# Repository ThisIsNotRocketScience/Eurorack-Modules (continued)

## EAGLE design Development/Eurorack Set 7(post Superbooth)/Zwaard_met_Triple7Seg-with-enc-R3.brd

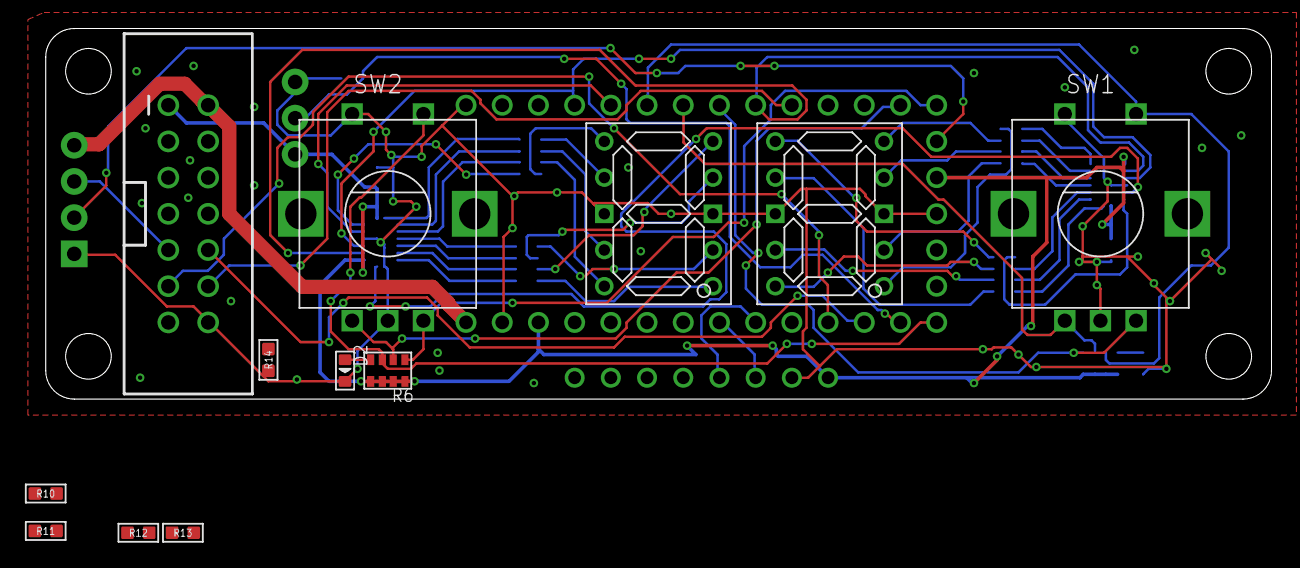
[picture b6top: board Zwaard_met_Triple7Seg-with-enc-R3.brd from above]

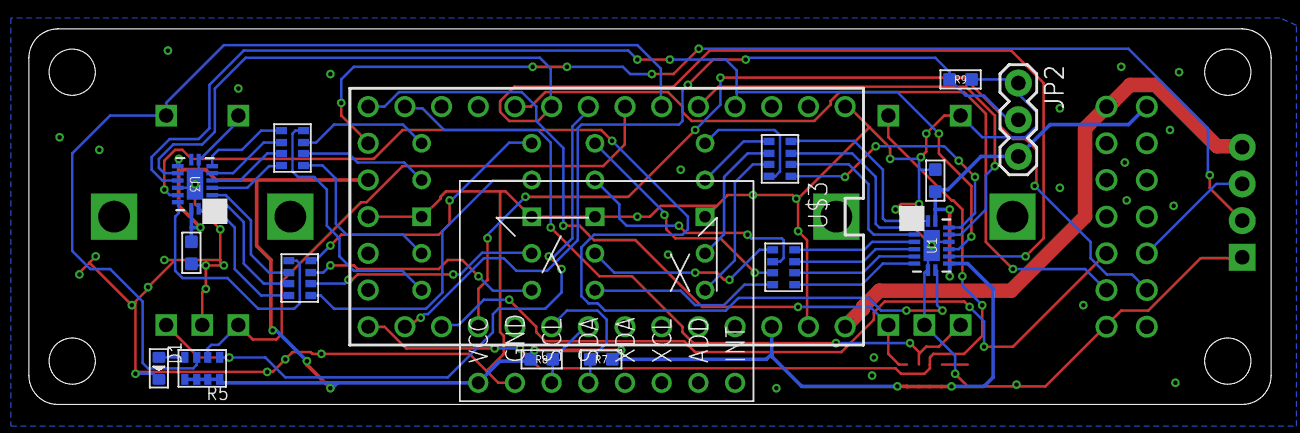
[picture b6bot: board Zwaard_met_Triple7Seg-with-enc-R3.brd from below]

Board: 2 copper layers, 86.0 x 26.0 mm, 29 parts (16 on the bottom side), 61 nets.

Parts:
C1, C2: 100n; C0603
D1, D2: LED0603
JP1: 1X04
JP2: 1X03
R1, R2, R3, R4: 56; R1206-8
R5, R6: R1206-8
R7, R8: 2k; R0603
R9, R10, R11, R12, R13, R14: 10k; R0603
SW1, SW2: EC12E_SW; ALPS_EC12E_SW
U1, U3: 74HCT595BQ; QFN50P250X350X100-17N
U$1, U$4: 7.1SEG; 7SEG_500X400MIL
U$3: TEENSY_LC_OUTER_ROW; TEENSY_3.0-3.2&LC_OUTER_ROW
U$6: ACCELERO; ACCELBOARD
U$7: M07X2; 2X70SHROUDED_LOCK

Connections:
3.3V: C1.1, C2.1, JP2.3, R5.5, R5.6, R5.7, R5.8, R6.5, R6.6, R6.7, R6.8, R7.1, R8.1, U1.10, U1.16, U3.10, U3.16, U$3.3.3V, U$3.3.3V1, U$6.VCC, U$7.1
5V: JP1.4, U$3.VIN, U$7.2
A: R1.8, U$1.1
A2: R3.8, U$4.1
B: R1.5, U$1.2
B2: R3.5, U$4.2
C: R1.6, U$1.3
C2: R3.6, U$4.3
D: R1.7, U$1.4
D2: R3.7, U$4.4
E: R2.5, U$1.6
E2: R4.5, U$4.6
ENC1_A: R5.2, SW1.A, U$3.5
ENC1_B: R5.1, SW1.B, U$3.6
ENC1_S: R5.3, SW1.E, U$3.4
ENC2_A: R6.2, SW2.A, U$3.11
ENC2_B: R6.1, SW2.B, U$3.12
ENC2_S: R6.3, SW2.E, U$3.13
F: R2.6, U$1.7
F2: R4.6, U$4.7
G: R2.7, U$1.8
G2: R4.7, U$4.8
GND: C1.2, C2.2, D1.-, D2.-, JP1.1, JP2.1, R9.1, R12.1, SW1.C, SW1.D, SW2.C, SW2.D, U1.8, U1.13, U1.17, U3.8, U3.13, U3.17, U$1.GNDA, U$1.GNDB, U$3.AGND, U$3.GND, U$3.GND1, U$4.GNDA, U$4.GNDB, U$6.GND, U$7.14
H: R2.8, U$1.5
H2: R4.8, U$4.5
LED1: R10.1, U$3.9
LED1OUT: R10.2, U$7.3
LED2: R11.1, U$3.10
LED2OUT: R11.2, U$7.4
LEDCLK: U1.11, U3.11, U$3.7
LEDDAT: U1.14, U$3.3
LEDLATCH: U1.12, U3.12, U$3.2
LED_DATA_OUT: JP1.2, U$3.VBAT
LED_NAAR_RING: JP1.3, U$7.9
unnamed: D1.+, R5.4
unnamed: D2.+, R6.4
unnamed: R1.4, U1.1
unnamed: R1.3, U1.2
unnamed: R1.2, U1.3
unnamed: R2.4, U1.4
unnamed: R2.3, U1.5
unnamed: R2.2, U1.6
unnamed: R2.1, U1.7
unnamed: R1.1, U1.15
unnamed: R3.4, U3.1
unnamed: R3.3, U3.2
unnamed: R3.2, U3.3
unnamed: R4.4, U3.4
unnamed: R4.3, U3.5
unnamed: R4.2, U3.6
unnamed: R4.1, U3.7
unnamed: R3.1, U3.15
unnamed: R12.2, R13.1
POT1: R14.2, U$7.10
POT_1_IN: R13.2, R14.1, U$3.15/A1
POT_2: U$3.16/A2, U$7.11
SCL: R8.2, U$3.19/A5, U$6.SCL
SDA: R7.2, U$3.18/A4, U$6.SDA
SEG2DAT: U1.9, U3.14
SOFTPOT: JP2.2, R9.2, U$3.14/A0
SWITCH: U$3.8, U$7.12

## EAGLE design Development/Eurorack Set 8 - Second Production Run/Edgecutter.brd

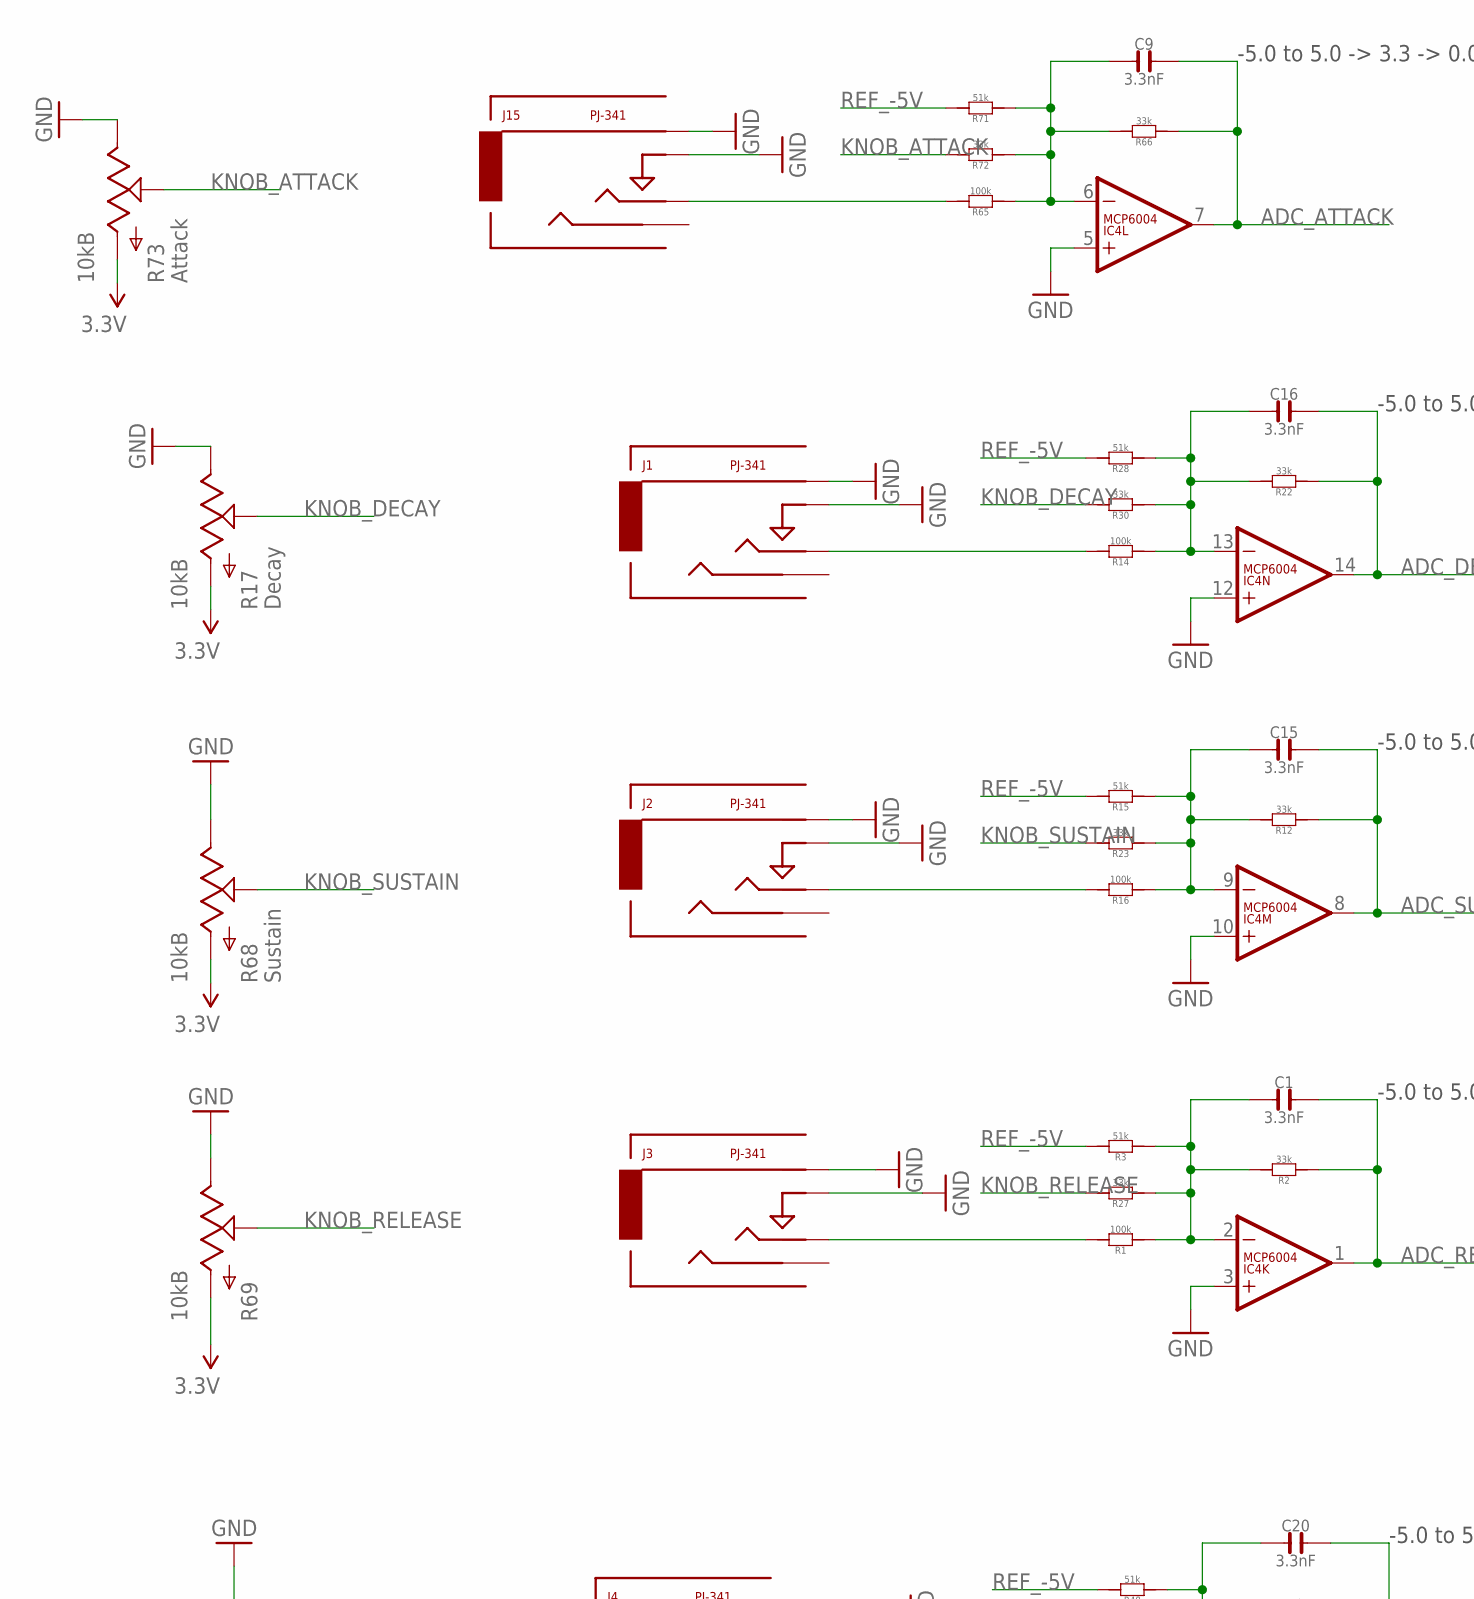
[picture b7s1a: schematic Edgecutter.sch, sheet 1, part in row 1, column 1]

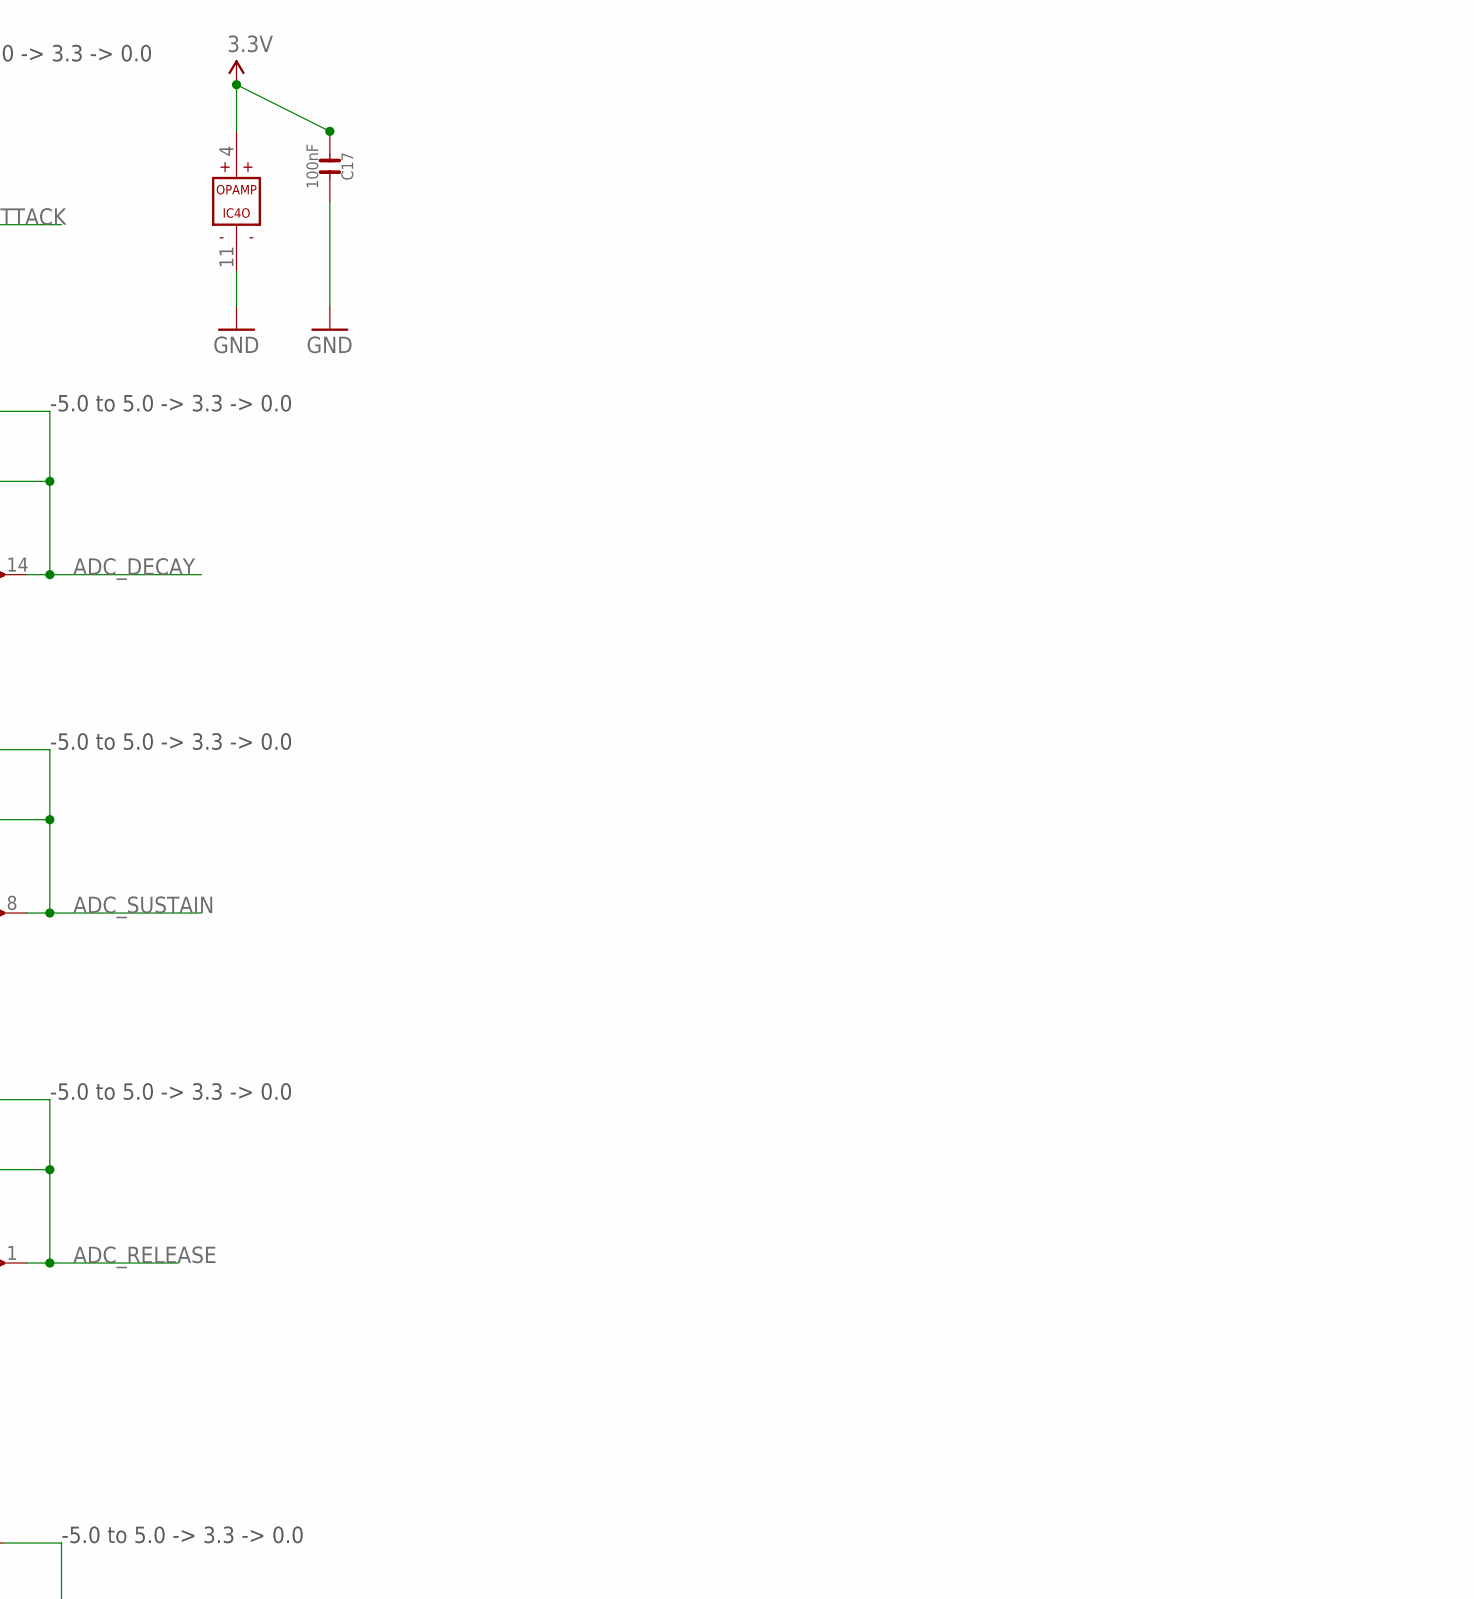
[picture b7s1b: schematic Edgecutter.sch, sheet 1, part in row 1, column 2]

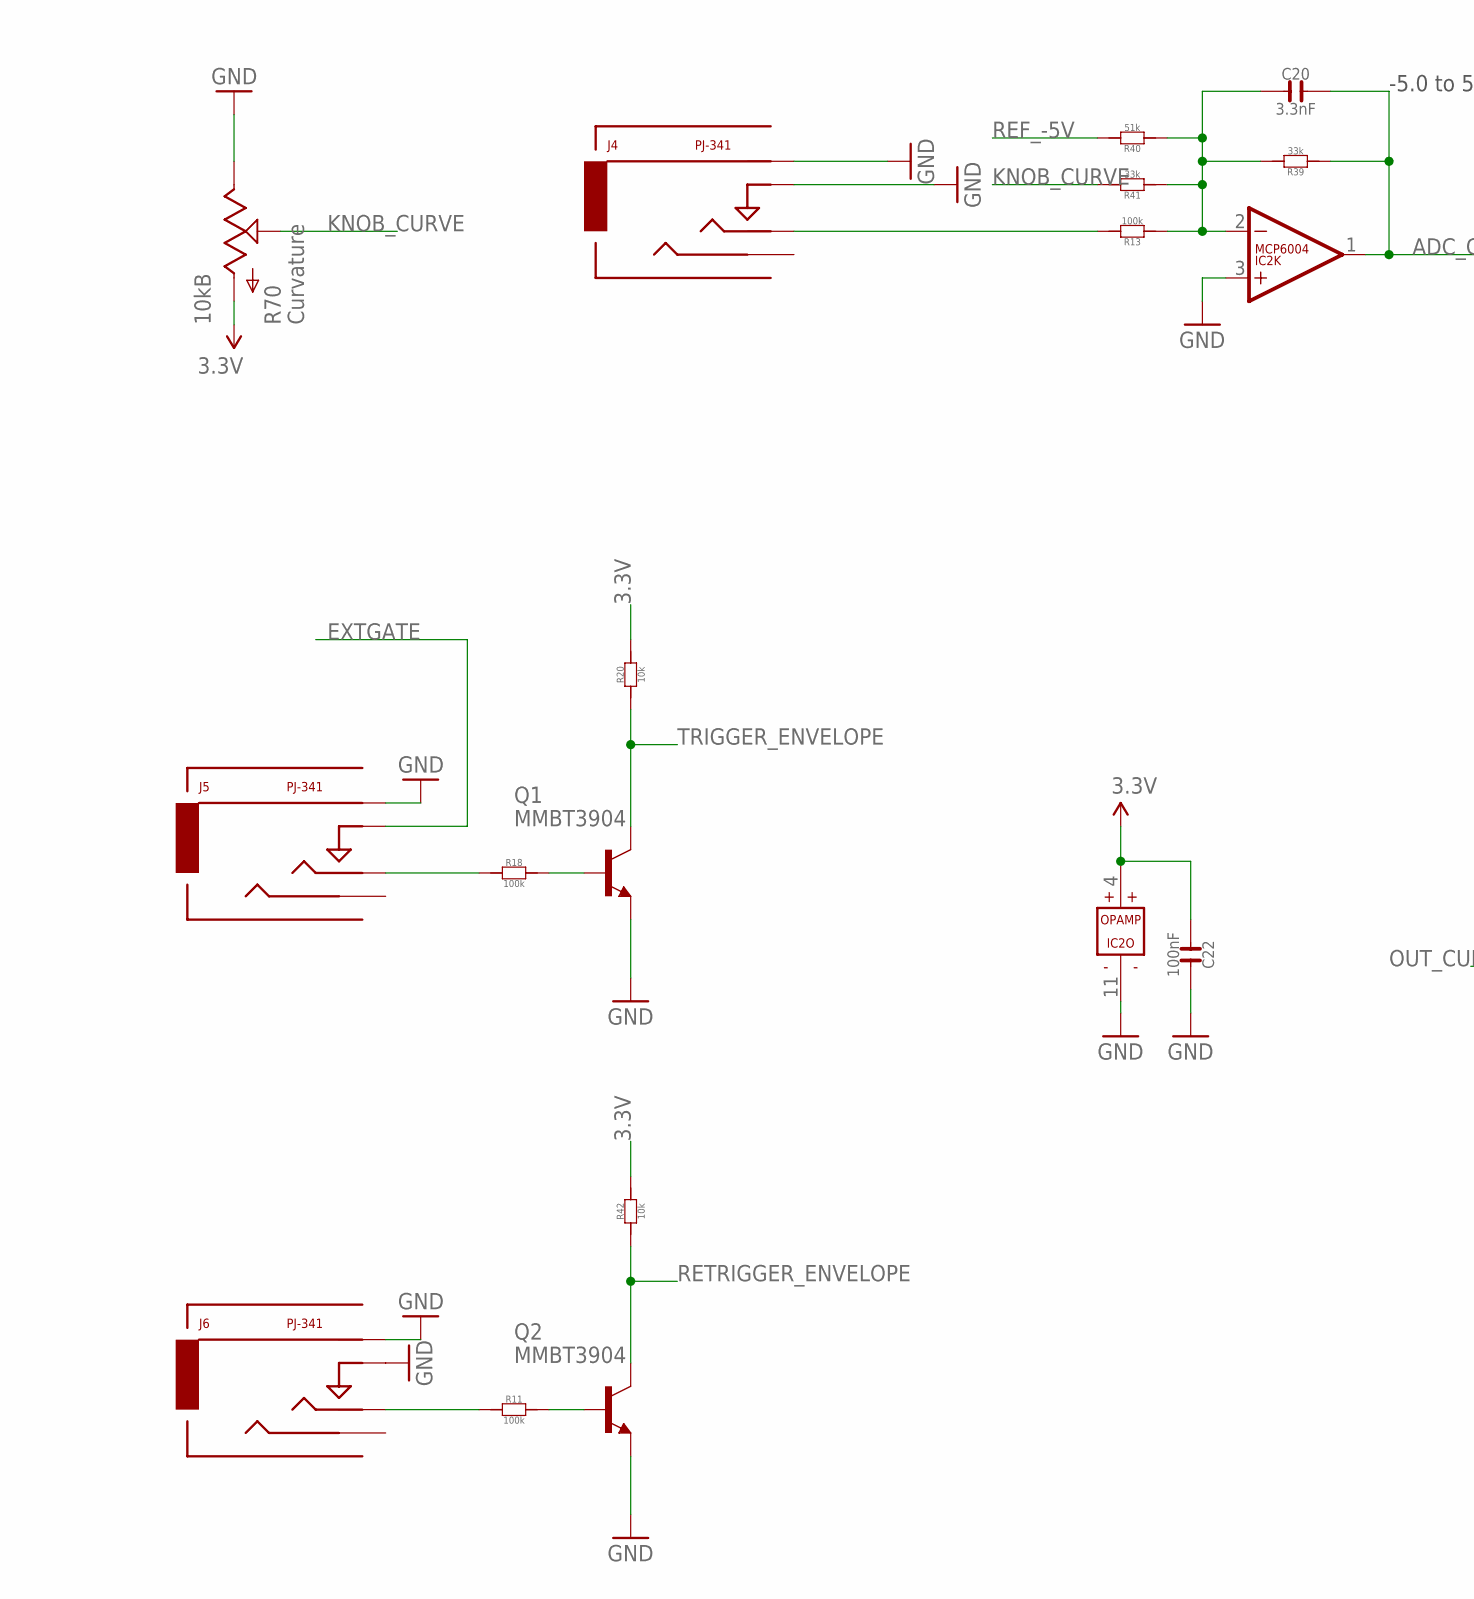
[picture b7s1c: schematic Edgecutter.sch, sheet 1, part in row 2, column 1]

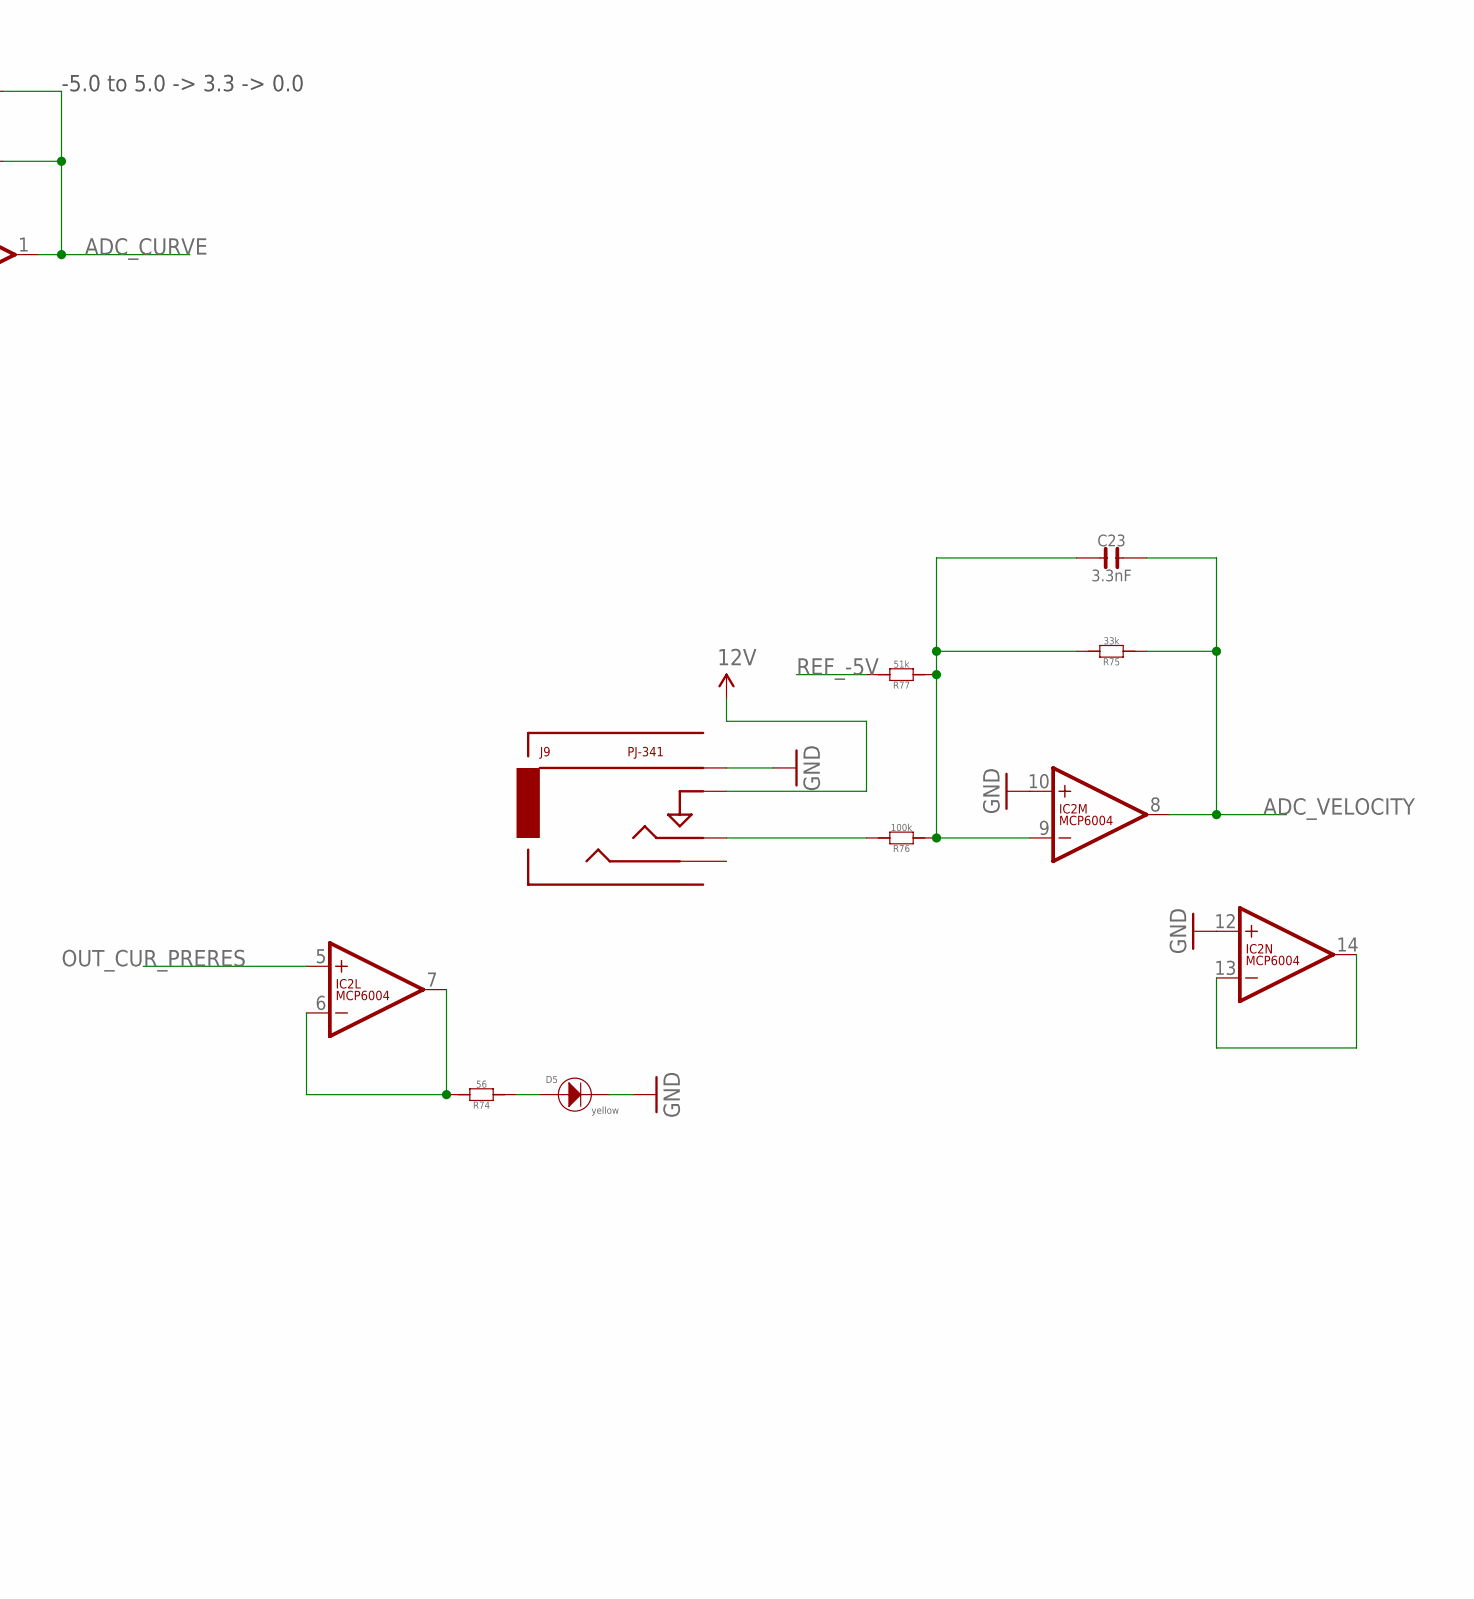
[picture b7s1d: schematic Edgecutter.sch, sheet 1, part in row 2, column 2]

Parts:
C1, C9, C15, C16, C20, C23: 3.3nF; C0603
C17, C22: 100nF; C0603; MPN MC0603F104Z160CT
D5: yellow; 3MMLED
IC2, IC4: MCP6004; SO14; MPN MCP6004-I/SL.
J1, J2, J3, J4, J5, J6, J9, J15: PJ-341; 3.5MM-JACK-SWITCH-13MM-INPUT
Q1, Q2: MMBT3904; SOT23-BEC; MPN PMBT3904,215
R1, R11, R13, R14, R16, R18, R65, R76: 100k; R0603
R2, R12, R22, R23, R27, R30, R39, R41, R66, R72, R75: 33k; R0603
R3, R15, R28, R40, R71, R77: 51k; R0603
R17, R68, R69, R70, R73: 10kB; OG-POTS_ALPS_POT_VERTICAL
R20, R42: 10k; R0603
R74: 56; R0603

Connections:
3.3V: C17.1, C22.1, IC2.4 (V+), IC4.4 (V+), R17.P$3 (A), R20.2, R42.2, R68.P$3 (A), R69.P$3 (A), R70.P$3 (A), R73.P$3 (A); also elsewhere on the board
12V: J9.SWITCH@3 (SWITCH); also elsewhere on the board
ADC_ATTACK: C9.2, IC4.7 (OUT), R66.1; also elsewhere on the board
ADC_CURVE: C20.2, IC2.1 (OUT), R39.1; also elsewhere on the board
ADC_DECAY: C16.2, IC4.14 (OUT), R22.1; also elsewhere on the board
ADC_RELEASE: C1.2, IC4.1 (OUT), R2.1; also elsewhere on the board
ADC_SUSTAIN: C15.2, IC4.8 (OUT), R12.1; also elsewhere on the board
ADC_VELOCITY: C23.2, IC2.8 (OUT), R75.1; also elsewhere on the board
EXTGATE: J5.SWITCH@3 (SWITCH); also elsewhere on the board
GND: C17.2, C22.2, D5.-, IC2.3 (+IN), IC2.10 (+IN), IC2.11 (V-), IC2.12 (+IN), IC4.3 (+IN), IC4.5 (+IN), IC4.10 (+IN), IC4.11 (V-), IC4.12 (+IN), J1.RING@3 (RING), J1.SWITCH@3 (SWITCH), J2.RING@3 (RING), J2.SWITCH@3 (SWITCH), J3.RING@3 (RING), J3.SWITCH@3 (SWITCH), J4.RING@3 (RING), J4.SWITCH@3 (SWITCH), J5.RING@3 (RING), J6.RING@3 (RING), J6.SWITCH@3 (SWITCH), J9.RING@3 (RING), J15.RING@3 (RING), J15.SWITCH@3 (SWITCH), Q1.E, Q2.E, R17.P$1 (E), R68.P$1 (E), R69.P$1 (E), R70.P$1 (E), R73.P$1 (E); also elsewhere on the board
KNOB_ATTACK: R72.2, R73.P$2 (S)
KNOB_CURVE: R41.2, R70.P$2 (S)
KNOB_DECAY: R17.P$2 (S), R30.2
KNOB_RELEASE: R27.2, R69.P$2 (S)
KNOB_SUSTAIN: R23.2, R68.P$2 (S)
unnamed: J2.TIP@3 (TIP), R16.2
unnamed: C15.1, IC4.9 (-IN), R12.2, R15.1, R16.1, R23.1
unnamed: J3.TIP@3 (TIP), R1.2
unnamed: C1.1, IC4.2 (-IN), R1.1, R2.2, R3.1, R27.1
unnamed: J15.TIP@3 (TIP), R65.2
unnamed: J4.TIP@3 (TIP), R13.2
unnamed: Q1.B, R18.2
unnamed: J5.TIP@3 (TIP), R18.1
unnamed: IC2.6 (-IN), IC2.7 (OUT), R74.2
unnamed: C9.1, IC4.6 (-IN), R65.1, R66.2, R71.1, R72.1
unnamed: IC2.13 (-IN), IC2.14 (OUT)
unnamed: J1.TIP@3 (TIP), R14.2
unnamed: C16.1, IC4.13 (-IN), R14.1, R22.2, R28.1, R30.1
unnamed: Q2.B, R11.2
unnamed: C20.1, IC2.2 (-IN), R13.1, R39.2, R40.1, R41.1
unnamed: J6.TIP@3 (TIP), R11.1
unnamed: C23.1, IC2.9 (-IN), R75.2, R76.1, R77.1
unnamed: D5.+, R74.1
unnamed: J9.TIP@3 (TIP), R76.2
OUT_CUR_PRERES: IC2.5 (+IN); also elsewhere on the board
REF_-5V: R3.2, R15.2, R28.2, R40.2, R71.2, R77.2; also elsewhere on the board
RETRIGGER_ENVELOPE: Q2.C, R42.1; also elsewhere on the board
TRIGGER_ENVELOPE: Q1.C, R20.1; also elsewhere on the board

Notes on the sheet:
-5.0 to 5.0 -> 3.3 -> 0.0

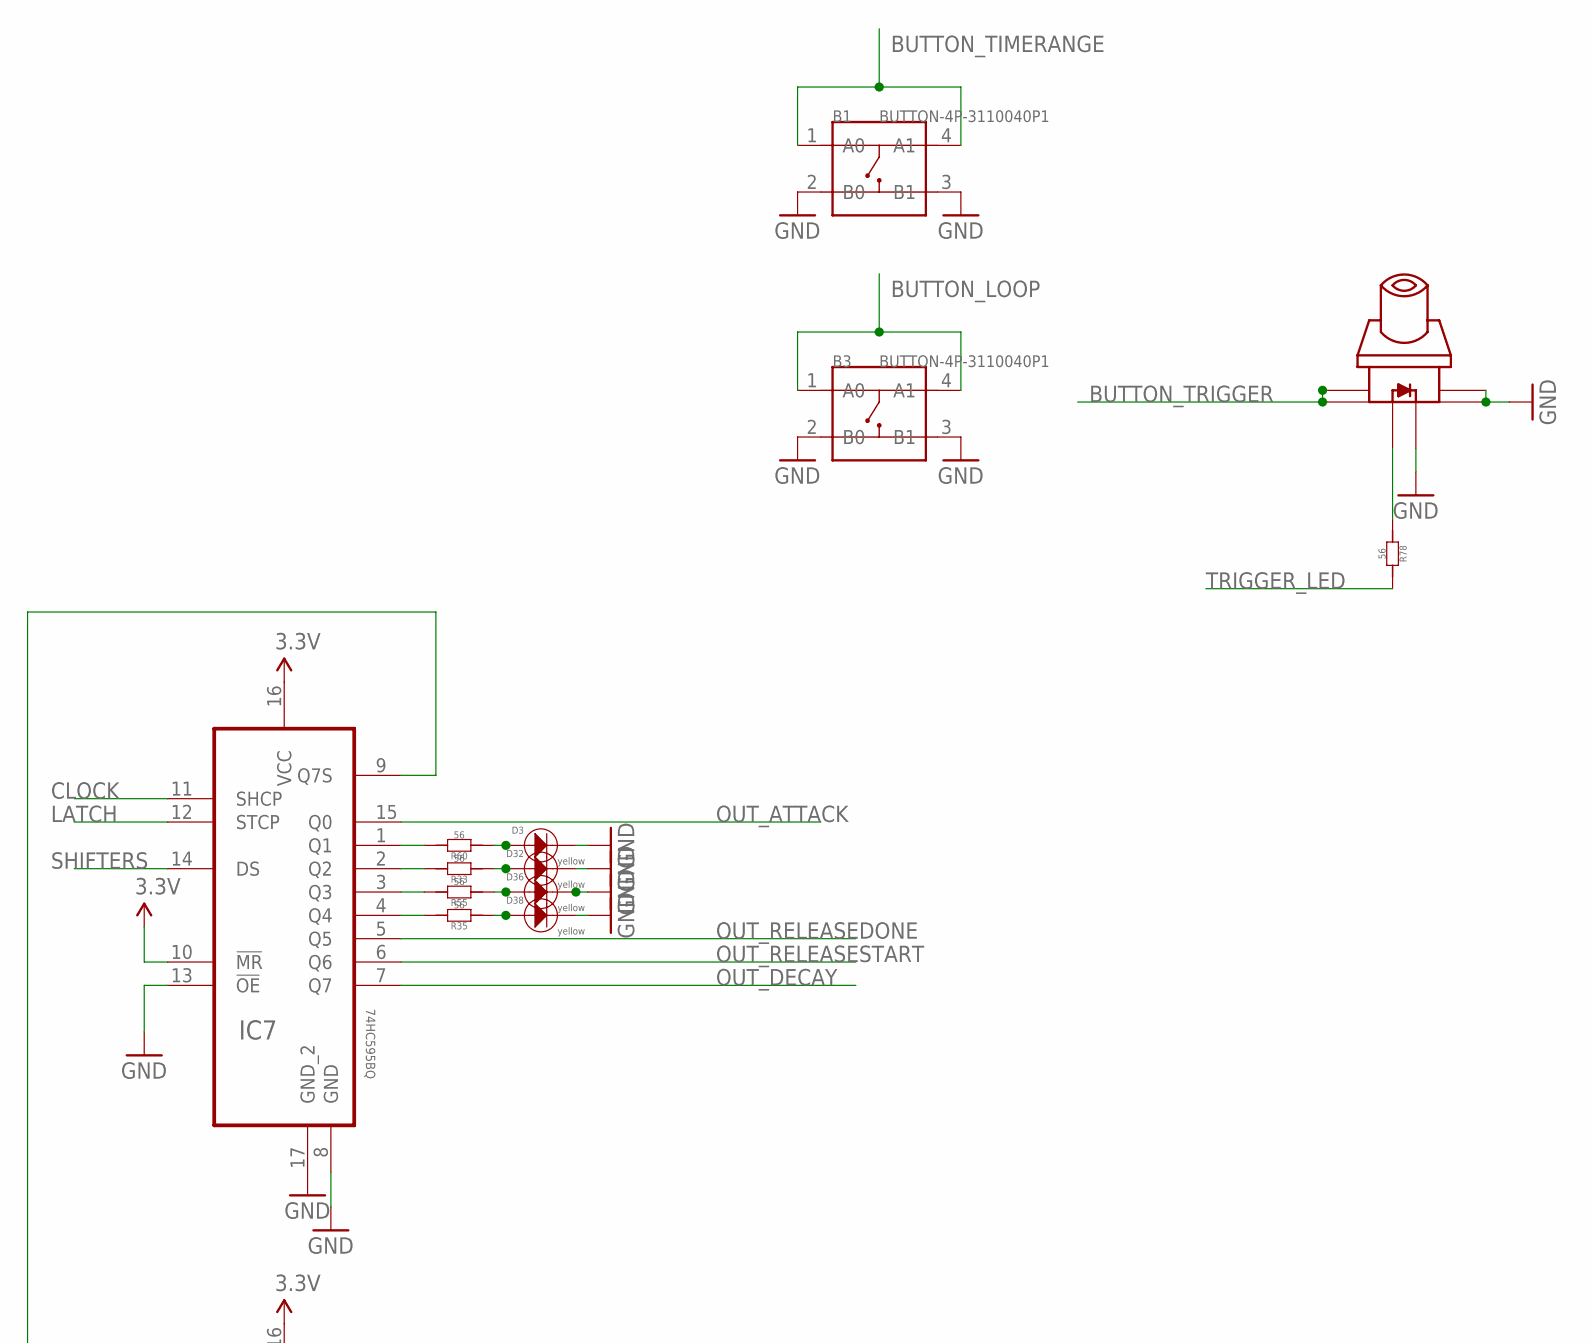
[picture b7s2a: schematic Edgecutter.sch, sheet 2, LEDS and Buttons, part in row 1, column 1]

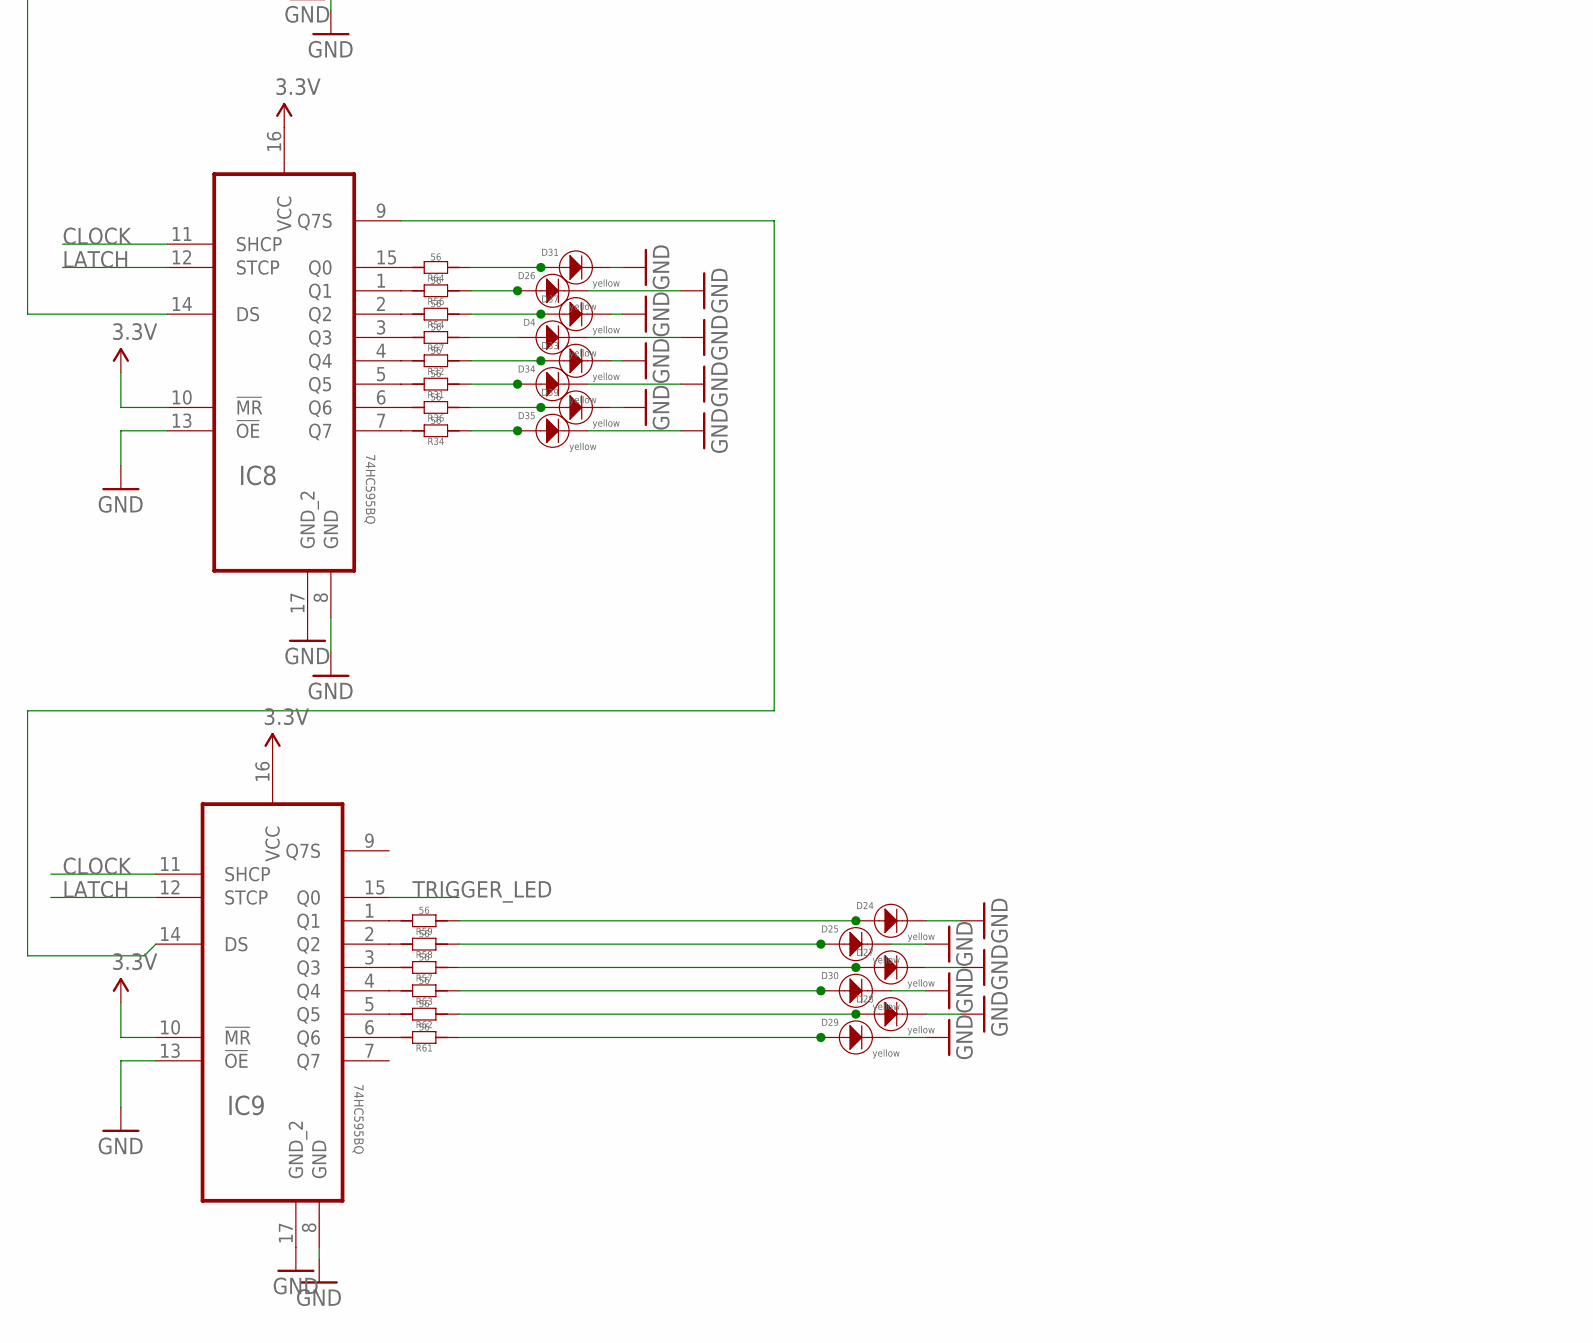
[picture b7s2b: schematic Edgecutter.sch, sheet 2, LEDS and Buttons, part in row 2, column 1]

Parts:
B1, B3: BUTTON-4P-3110040P1; 4P-6.0X6.0X5.0H
D3, D4, D24, D25, D26, D27, D28, D29, D30, D31, D32, D33, D34, D35, D36, D37, D38, D39: yellow; 3MMLED
IC7, IC8, IC9: 74HC595BQ; QFN50P250X350X100-17N
R31, R32, R33, R34, R35, R36, R54, R55, R56, R57, R58, R59, R60, R61, R62, R63, R64, R67, R78: 56; R0603
U$2: SWITCH_W_LED_PB6149L-X-102YELLOW; PB6149L

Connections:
3.3V: IC7.10 (!MR), IC7.16 (VCC), IC8.10 (!MR), IC8.16 (VCC), IC9.10 (!MR), IC9.16 (VCC); also elsewhere on the board
BUTTON_LOOP: B3.1 (A0), B3.4 (A1); also elsewhere on the board
BUTTON_TIMERANGE: B1.1 (A0), B1.4 (A1); also elsewhere on the board
BUTTON_TRIGGER: U$2.1, U$2.2; also elsewhere on the board
CLOCK: IC7.11 (SHCP), IC8.11 (SHCP), IC9.11 (SHCP); also elsewhere on the board
GND: B1.2 (B0), B1.3 (B1), B3.2 (B0), B3.3 (B1), D3.-, D4.-, D24.-, D25.-, D26.-, D27.-, D28.-, D29.-, D30.-, D31.-, D32.-, D33.-, D34.-, D35.-, D36.-, D37.-, D38.-, D39.-, IC7.8 (GND), IC7.13 (!OE), IC7.17 (GND_2), IC8.8 (GND), IC8.13 (!OE), IC8.17 (GND_2), IC9.8 (GND), IC9.13 (!OE), IC9.17 (GND_2), U$2.3, U$2.4, U$2.LEDNEG (NEG); also elsewhere on the board
LATCH: IC7.12 (STCP), IC8.12 (STCP), IC9.12 (STCP); also elsewhere on the board
unnamed: R78.1, U$2.LEDPOS (POS)
unnamed: IC8.7 (Q7), R34.2
unnamed: IC8.15 (Q0), R64.2
unnamed: D28.+, R62.1
unnamed: D4.+, R67.1
unnamed: IC7.1 (Q1), R60.2
unnamed: D29.+, R61.1
unnamed: IC7.2 (Q2), R33.2
unnamed: IC7.3 (Q3), R55.2
unnamed: IC7.4 (Q4), R35.2
unnamed: IC8.1 (Q1), R56.2
unnamed: IC8.2 (Q2), R54.2
unnamed: IC8.3 (Q3), R67.2
unnamed: IC8.4 (Q4), R32.2
unnamed: IC8.5 (Q5), R31.2
unnamed: IC8.6 (Q6), R36.2
unnamed: IC9.1 (Q1), R59.2
unnamed: IC9.2 (Q2), R58.2
unnamed: D3.+, R60.1
unnamed: IC9.3 (Q3), R57.2
unnamed: IC9.4 (Q4), R63.2
unnamed: IC9.5 (Q5), R62.2
unnamed: IC9.6 (Q6), R61.2
unnamed: D27.+, R57.1
unnamed: D26.+, R56.1
unnamed: D25.+, R58.1
unnamed: D24.+, R59.1
unnamed: D30.+, R63.1
unnamed: D31.+, R64.1
unnamed: D32.+, R33.1
unnamed: D33.+, R32.1
unnamed: D34.+, R31.1
unnamed: D35.+, R34.1
unnamed: D36.+, R55.1
unnamed: D37.+, R54.1
unnamed: D38.+, R35.1
unnamed: D39.+, R36.1
OUT_ATTACK: IC7.15 (Q0); also elsewhere on the board
OUT_DECAY: IC7.7 (Q7); also elsewhere on the board
OUT_RELEASEDONE: IC7.5 (Q5); also elsewhere on the board
OUT_RELEASESTART: IC7.6 (Q6); also elsewhere on the board
SHIFTER1TO2: IC7.9 (Q7S), IC8.14 (DS)
SHIFTER2TO3: IC8.9 (Q7S), IC9.14 (DS)
SHIFTERS: IC7.14 (DS); also elsewhere on the board
TRIGGER_LED: IC9.15 (Q0), R78.2

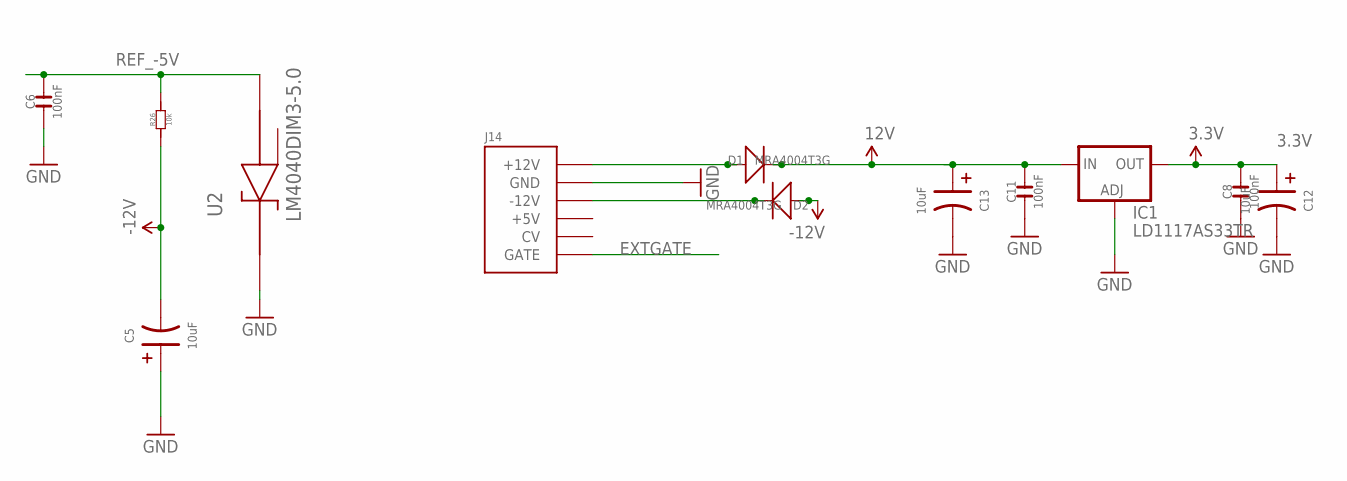
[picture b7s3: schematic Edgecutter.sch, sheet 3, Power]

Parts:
C5, C12, C13: 10uF; AVX-A; MPN TAJB106K020RNJ
C6: 100nF; C0603; MPN 06035C104KAT2A
C8, C11: 100nF; C0603; MPN MC0603F104Z160CT
D1, D2: MRA4004T3G; DO-214AC; MPN US1G-E3/5AT
IC1: LD1117AS33TR; SOT223; MPN LD1117AS33TR
J14: POWERSMT; 2X08_SMT_HEADER
R26: 10k; R0603
U2: LM4040DIM3-5.0; SOT95P237X112-3N

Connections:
3.3V: C8.2, C12.+ (1), IC1.2 (OUT), IC1.4 (OUT); also elsewhere on the board
12V: C11.2, C13.+ (1), D1.2 (-), IC1.3 (IN); also elsewhere on the board
-12V: C5.- (2), D2.1 (+), R26.1; also elsewhere on the board
EXTGATE: J14.15 (GATE), J14.16 (GATE); also elsewhere on the board
GND: C5.+ (1), C6.1, C8.1, C11.1, C12.- (2), C13.- (2), IC1.1 (ADJ), J14.3 (GND), J14.4 (GND), J14.5 (GND), J14.6 (GND), J14.7 (GND), J14.8 (GND), U2.1 (CATHODE); also elsewhere on the board
unnamed: D1.1 (+), J14.9 (+12V), J14.10 (+12V)
unnamed: D2.2 (-), J14.1 (-12V), J14.2 (-12V)
REF_-5V: C6.2, R26.2, U2.2 (ANODE); also elsewhere on the board
